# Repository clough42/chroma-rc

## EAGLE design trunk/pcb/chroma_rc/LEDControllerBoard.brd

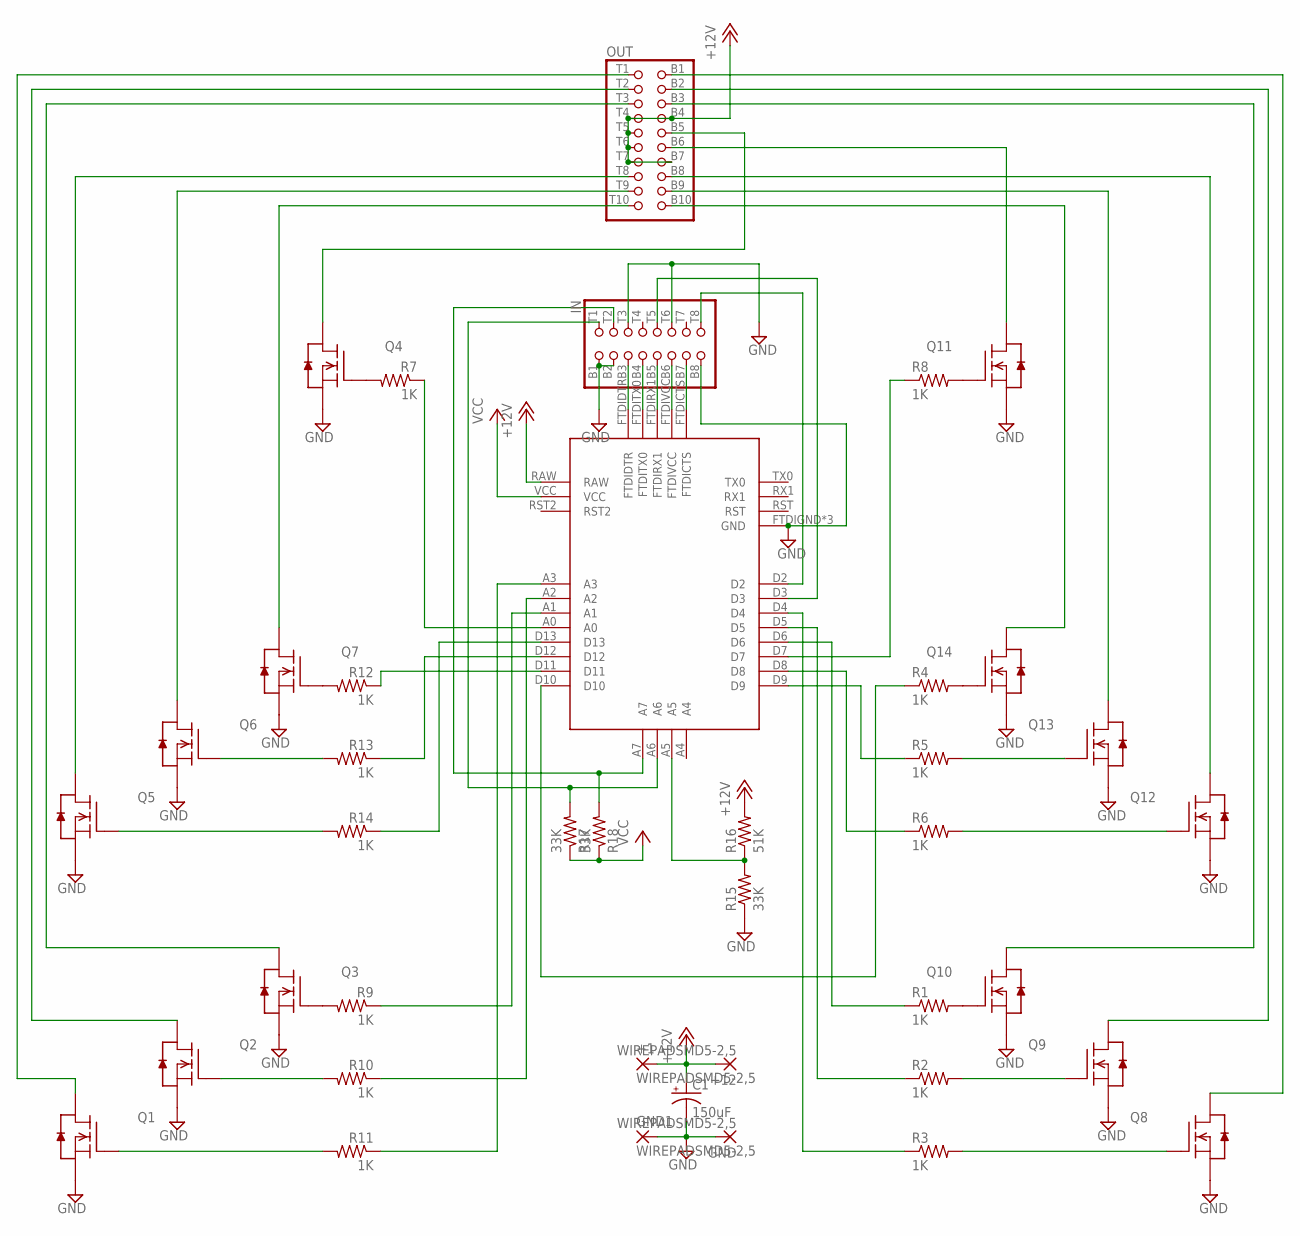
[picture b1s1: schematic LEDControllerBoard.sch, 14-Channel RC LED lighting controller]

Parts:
+1, +12: WIREPADSMD5-2,5; 5-2,5
C1: 150uF; PANASONIC_D
GND, GND1: WIREPADSMD5-2,5; 5-2,5
IN: 2X8/EDGE
OUT: 2X10/EDGE
Q1, Q2, Q3, Q4, Q5, Q6, Q7, Q8, Q9, Q10, Q11, Q12, Q13, Q14: FDC653NSSOT6; SSOT6
R1, R2, R3, R4, R5, R6, R7, R8, R9, R10, R11, R12, R13, R14: 1K; R0603
R15, R17, R18: 33K; R0603
R16: 51K; R0603
U$15: ARDUINOPROMINI

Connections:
+12V: +1.1, +12.1, C1.+, OUT.B4 (8), OUT.B7 (14), OUT.T4 (7), OUT.T5 (9), OUT.T6 (11), OUT.T7 (13), R16.2, U$15.RAW
GND: C1.-, GND.1, GND1.1, IN.B1 (2), IN.B2 (4), IN.B8 (16), IN.T3 (5), IN.T6 (11), Q1.4 (S), Q2.4 (S), Q3.4 (S), Q4.4 (S), Q5.4 (S), Q6.4 (S), Q7.4 (S), Q8.4 (S), Q9.4 (S), Q10.4 (S), Q11.4 (S), Q12.4 (S), Q13.4 (S), Q14.4 (S), R15.1, U$15.FTDIGND (GND), U$15.GND, U$15.GND2 (GND)
unnamed: Q10.3 (G), R1.2
unnamed: Q9.3 (G), R2.2
unnamed: OUT.B5 (10), Q4.1 (D), Q4.2 (D), Q4.5 (D), Q4.6 (D)
unnamed: OUT.B10 (20), Q14.1 (D), Q14.2 (D), Q14.5 (D), Q14.6 (D)
unnamed: Q8.3 (G), R3.2
unnamed: OUT.B9 (18), Q13.1 (D), Q13.2 (D), Q13.5 (D), Q13.6 (D)
unnamed: Q14.3 (G), R4.2
unnamed: Q13.3 (G), R5.2
unnamed: OUT.B8 (16), Q12.1 (D), Q12.2 (D), Q12.5 (D), Q12.6 (D)
unnamed: OUT.B3 (6), Q10.1 (D), Q10.2 (D), Q10.5 (D), Q10.6 (D)
unnamed: OUT.B2 (4), Q9.1 (D), Q9.2 (D), Q9.5 (D), Q9.6 (D)
unnamed: Q12.3 (G), R6.2
unnamed: OUT.B1 (2), Q8.1 (D), Q8.2 (D), Q8.5 (D), Q8.6 (D)
unnamed: OUT.B6 (12), Q11.1 (D), Q11.2 (D), Q11.5 (D), Q11.6 (D)
unnamed: R10.1, U$15.A2
unnamed: OUT.T10 (19), Q7.1 (D), Q7.2 (D), Q7.5 (D), Q7.6 (D)
unnamed: OUT.T9 (17), Q6.1 (D), Q6.2 (D), Q6.5 (D), Q6.6 (D)
unnamed: Q3.3 (G), R9.2
unnamed: Q4.3 (G), R7.2
unnamed: Q11.3 (G), R8.2
unnamed: Q2.3 (G), R10.2
unnamed: OUT.T8 (15), Q5.1 (D), Q5.2 (D), Q5.5 (D), Q5.6 (D)
unnamed: OUT.T3 (5), Q3.1 (D), Q3.2 (D), Q3.5 (D), Q3.6 (D)
unnamed: Q1.3 (G), R11.2
unnamed: OUT.T2 (3), Q2.1 (D), Q2.2 (D), Q2.5 (D), Q2.6 (D)
unnamed: Q7.3 (G), R12.2
unnamed: Q6.3 (G), R13.2
unnamed: OUT.T1 (1), Q1.1 (D), Q1.2 (D), Q1.5 (D), Q1.6 (D)
unnamed: IN.B7 (14), U$15.FTDICTS
unnamed: Q5.3 (G), R14.2
unnamed: IN.B6 (12), U$15.FTDIVCC
unnamed: IN.B5 (10), U$15.FTDIRX1
unnamed: R3.1, U$15.D4
unnamed: R2.1, U$15.D5
unnamed: R1.1, U$15.D6
unnamed: R6.1, U$15.D8
unnamed: R5.1, U$15.D9
unnamed: R4.1, U$15.D10
unnamed: R7.1, U$15.A0
unnamed: R8.1, U$15.D7
unnamed: R15.2, R16.1, U$15.A5
unnamed: IN.T5 (9), U$15.D3
unnamed: R9.1, U$15.A1
unnamed: R11.1, U$15.A3
unnamed: R12.1, U$15.D11
unnamed: R14.1, U$15.D13
unnamed: R13.1, U$15.D12
unnamed: IN.T2 (3), R18.2, U$15.A7
unnamed: IN.T8 (15), U$15.D2
unnamed: IN.B4 (8), U$15.FTDITX0
unnamed: IN.B3 (6), U$15.FTDIDTR
unnamed: IN.T1 (1), R17.2, U$15.A6
VCC: R17.1, R18.1, U$15.VCC

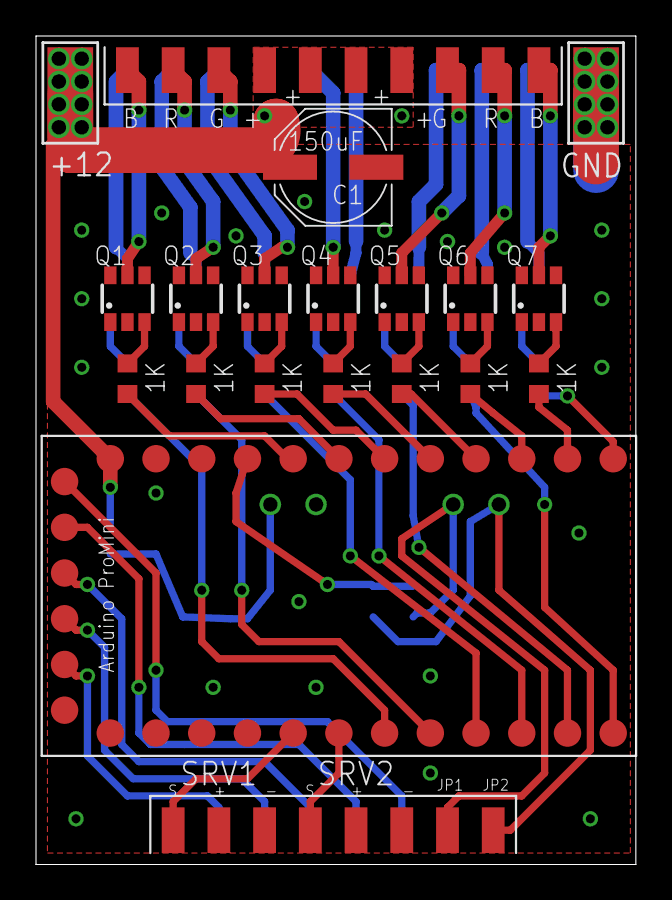
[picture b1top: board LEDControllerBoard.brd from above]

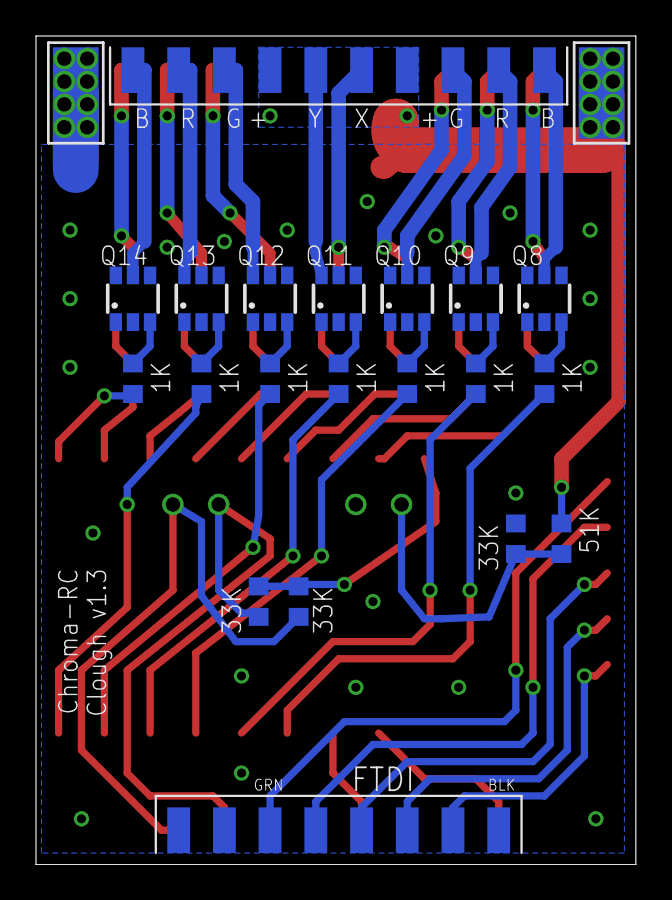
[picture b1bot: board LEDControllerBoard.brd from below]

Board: 2 copper layers, 33.3 x 46.0 mm, 40 parts (20 on the bottom side), 55 nets.

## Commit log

2013-11-05 Initial directory structure.
2013-11-05 Initial sketch, with hardware configuration.
2013-11-17 Renamed folder to use underscore for consistency.
2013-11-17 Split up files into cpp/h for main and hardware.
2013-11-17 PCB v1.3. Added second set of power pads on the bottom.
2013-11-20 Add IDE template for Eclipse, based on a similar setup in MultiWii.
2013-11-20 Converted project over to Chroma-rc.
2013-11-21 Added externals reference to check out the chroma_rc source under the Eclipse environment.
2013-11-22 AVR programmer setup.
2013-11-22 Prototype white with pulsing lights.
2013-11-22 Add reading of servo inputs. Add two sequences, blackout, orientation and landing lights
2013-11-22 Flatten into a single directory for Arduino IDE sanity. Add two fixed color schemes.
2013-11-24 Add red/green fade sequence. Move data tables to program memory.
2013-11-24 Stub SoftPWM library.
2013-11-24 Rename project.
2013-11-24 Add SoftPWM
2013-11-24 Switch everything over to PWM. Implement five color sequences.
2013-11-24 Add self-test sequence on startup.
2013-11-24 Fix fault that was occurring during startup. Initialize servos first and give time to get a full pulse. Protect against out-of-range servo values.
2015-03-14 Migrating wiki contents from Google Code
